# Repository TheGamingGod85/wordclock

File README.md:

# Wordclock
ESP32 based DIY wordclock project

> **60 cm fork:** see the [60 cm Full Build Guide](README-60cm.md) for the enlarged two-LED-per-letter version, or the [short plan](PLAN-60cm.md) for the decision list.

TL;DR: check out this :sparkles:[demo video](https://youtu.be/WF_X5soabm0) :sparkles:

<br/>
Another take on the classic DIY word clock. This one requires a laser cutter but promises a very clean result and is quite cheap to make (about 50 €) while being feature packed with its 11x10 RGB LED matrix, RTC module (time setting survives power loss), light sensor, WiFi connectivity and more. 

This project was designed for the tools available in our makerspace. The largest square that can be cut in an Epilog Mini laser cutter is approximately 30x30cm, so the clock is designed around that constraint.

<br/>

## Table of Contents

- [Project overview](#project-overview)
  * [Hardware](#hardware)
  * [Software](#software)
- [Bill Of Materials](#bill-of-materials)
  * [Electronics](#electronics)
  * [Frame](#frame)

## Project overview

### Hardware 

Building the clock from scratch involves mostly laser cutting and soldering. It is not technically challenging if you have basic soldering skills (and access to a laser cutter), but it does take time on both fronts. The project's hardware can be broken down in 3 major elements:

- __The faceplate__ is a glass panel from a cheap picture frame, that is spray painted on its back, then laser etched to mark the letters. The templates and instructions are located in [the faceplate subdirectory](hardware/faceplate/README.md).
- __The frame__ is a sandwich of laser-cut MDF boards. If could also be done with CEC or 3d printing. It holds everything together and most importantly the LED matrix. It has little wells for each LED to channel the light to the letters on the faceplate. The templates and assembly instructions are located in [the frame subdirectory](hardware/frame/README.md).
- __The electronics__ revolve around a WiFI enabled ESP32 development board and a matrix of 114 LEDs made from an LED strip. There is also an RTC module to keep track of time, and a light sensor (LDR). The schematics and instructions for assembly are located in [the electronics subdirectory](hardware/electronics/README.md).

You can oviously choose to customize any of the provided templates to eg create a different faceplate, or adapt the frame to your specific needs (change the LED layout, add extra sensors, etc).

#### Nodo clock

Alternatively, [nodo-shop.nl](https://nodo-shop.nl) developed and sells [a kit](https://www.nodo-shop.nl/en/52-wordclock) that is fully compatible with the software side of this project. 

The kit includes a 3D-printed faceplate (EN, FR and NL versions available) and custom circuit board, is very simple to assemble and requires no soldering.

### Software

The provided [source code](software/README.md) is using [PlatformIO](https://platformio.org/) and Arduino IDE. Here's a [demo video](https://youtu.be/WF_X5soabm0) (from v1.0, does not show all current features).

It runs a web server though a WiFi captive portal for initial configuration via a smartphone or computer, then optionally connects to your home network to use internet time (NTP), MQTT client for home automation, and other features. Check out the [User's Manual](software/UsersManual.md) for more details.

It is, of course, possible to ditch that code entirely and use [ESPHome](https://esphome.io/) or [MicroPython](https://docs.micropython.org/en/latest/esp32/tutorial/intro.html) instead. 

## Bill Of Materials

### Electronics

| Designation | Sample purchase link | Price |  
| ----------- | -------------------- | ----- |  
| ESP32 (WROOM32) microcontroller | [amazon.fr](https://www.amazon.fr/gp/product/B06XWVS2SJ/ref=ox_sc_act_title_6?smid=A3OY00ITR6XRNR&psc=1) | 5,99 € |
| DS3231 RTC module | [amazon.fr](https://www.amazon.fr/gp/product/B07DK5M5VW/) | 3,66 € |
| Level shifter 3.3 -> 5v | [amazon.fr](https://www.amazon.fr/gp/product/B07LG6RK7L) | 0,80 € |
| RGB addressable LEDs (WS2812), 60 per meter, 2 meters roll | [aliexpress.com](https://www.aliexpress.com/item/32958709980.html?spm=2114.search0104.3.35.2a616adcbmvvSU&ws_ab_test=searchweb0_0%2Csearchweb201602_4_10065_10130_10068_10547_319_317_10545_10696_10084_453_454_10083_10618_10307_10821_537_10302_536_10059_10884_10887_321_322_10103%2Csearchweb201603_53%2CppcSwitch_0&algo_expid=2a4f6a2a-c5bc-4435-a3ff-21b692aed5ff-7&algo_pvid=2a4f6a2a-c5bc-4435-a3ff-21b692aed5ff) | 4,17 € |
| 1000 uF capacitor | [amazon.fr](https://www.amazon.fr/gp/product/B01M4IUST7) | 0,40 € |
| Power supply (5V, 6A) | [aliexpress.com](https://fr.aliexpress.com/item/32835554243.html) | 6,99 € |
| Female barrel plug | [amazon.fr](https://www.amazon.fr/gp/product/B06XPBKC37) | 0,86 € |
| Light dependent resistor (LDR 5537) | [amazon.fr](https://www.amazon.fr/gp/product/B074QLFCF6/) | 0,08 € |
| Resistor 10k |
| Perfboard | [conrad.fr](https://www.conrad.fr/p/platine-dexperimentation-rademacher-wr-typ-908-1-vk-c-908-1-ep-epoxy-l-x-l-80-mm-x-50-mm-35-m-pas-254-mm-1-pcs-527309) | 3,36 € |
| Breakaway header pins | [amazon.fr](https://www.amazon.fr/gp/product/B07C3W8DGZ/ref=ppx_yo_dt_b_asin_title_o03_s00?ie=UTF8&psc=1) | 0,14 € |
| Wiring (silicon coating is recommended) |
| Solder |  
| Kapton + Electrical tape |
| Heatshrink tubing |
| Hot glue gun + glue sticks |

### Frame

| Designation | Sample purchase link | Price |  
| ----------- | -------------------- | ----- | 
| MDF boards, ~30.5 cm by 30.5+ cm, 3mm and 6mm thick | 615mm x 310mm boards, cut at Leroy Merlin | 5€ |
| Picture frame with glass panel, 30 by 30 cm | [leroymerlin.fr](https://www.leroymerlin.fr/v3/p/produits/cadre-clip-30-x-30-cm-e1500701594) | 2,99 € |
| Wood glue |
| Clamps |
| Spray paint (acrylic) |
| Edgeband |
| 1mm black felt layer | [amazon.fr](https://www.amazon.fr/dp/B07LFJNLZ9/) | 1,11 € |
| Ultra low profile VELCRO® strip or similar | [amazon.fr](https://www.amazon.fr/dp/B0728LKFGM/ref=pe_3044141_189395771_TE_dp_1) | 26 € |
| Black adhesive vinyl (just a small sheet) |
| Copper tape 51mm X 20m (optional) | [amazon.fr](https://www.amazon.fr/gp/product/B01MTQA0O6/ref=ppx_od_dt_b_asin_title_s00?ie=UTF8&psc=1) | 18,98 € |

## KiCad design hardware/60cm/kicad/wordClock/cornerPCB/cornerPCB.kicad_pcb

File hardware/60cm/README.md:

# 60 cm wordclock templates

Generated from the archived 30 cm design in `hardware/_archive_30cm/`.

Run `uv run 60cm` from this folder to regenerate every SVG. It writes into the folders below.

## Folders

| Folder | What is in it |
|---|---|
| `cut/` | The files to send to the cutter. These are the ones you need. |
| `backup/` | The original stencil outlines, kept in case Allerta does not cut well. |
| `preview/` | Layer-stack overlays and the font comparison image. Preview only — never cut these. |
| `fonts/` | The Google Fonts used for the stencil and comparisons (OFL licensed). |
| `electronics/` | `wordclock_60cm.fzz` circuit and its [wiring notes](electronics/README.md). |

## Files to cut

| File | Material | Notes |
|---|---|---|
| `cut/faceplate_clear_600.svg` | clear cast acrylic | Front sheet. Includes corner LED holes and two registration holes. |
| `cut/faceplate_EN_stencil_600.svg` | black acrylic | **Production cut file.** Allerta Stencil letters; bridges stop counter pieces falling out. |
| `cut/frame_cut1_600.svg` | 3 mm MDF | LED board support, with a bottom cavity for the controller. |
| `cut/frame_cut2_lightwells_600.svg` | 6 mm MDF | 110 wells: one per letter, scaled from the original hole. |
| `cut/frame_spacers_600.svg` | 6 mm MDF | One frame; cut as many layers as needed. |
| `cut/frame_back_600.svg` | back panel | Hatch and screw holes. |

## Backup

| File | Notes |
|---|---|
| `backup/faceplate_EN_stencil_original_600.svg` | The original 30 cm-derived letter outlines, as a cut-ready file. |

## Previews

| File | Notes |
|---|---|
| `preview/overlay_600.svg` | All six layers stacked with the production Allerta letters; legend lists them front to back. |
| `preview/overlay_original_stencil_600.svg` | Same stack with the backup original outlines. |
| `preview/overlay_stencil_font_600.svg` | Same stack, letters from Windows `STENCIL.TTF`. |
| `preview/overlay_BigShouldersStencilDisplay_600.svg` | Same stack, Google Fonts "Big Shoulders Stencil Display". |
| `preview/overlay_StardosStencil-Bold_600.svg` | Same stack, Google Fonts "Stardos Stencil Bold". |
| `preview/overlay_StardosStencil-Regular_600.svg` | Same stack, Google Fonts "Stardos Stencil Regular". |
| `preview/font_compare.png` | Side-by-side sample of all five fonts. |

All cut lines are red (`#ff0000`), fill none, 0.5 mm stroke. The sheets are 600 × 600 mm.

Registration holes at (15, 300) and (585, 300) line the two face sheets up, outside the spacer inner cut line. Corner LED holes are 12 mm across.

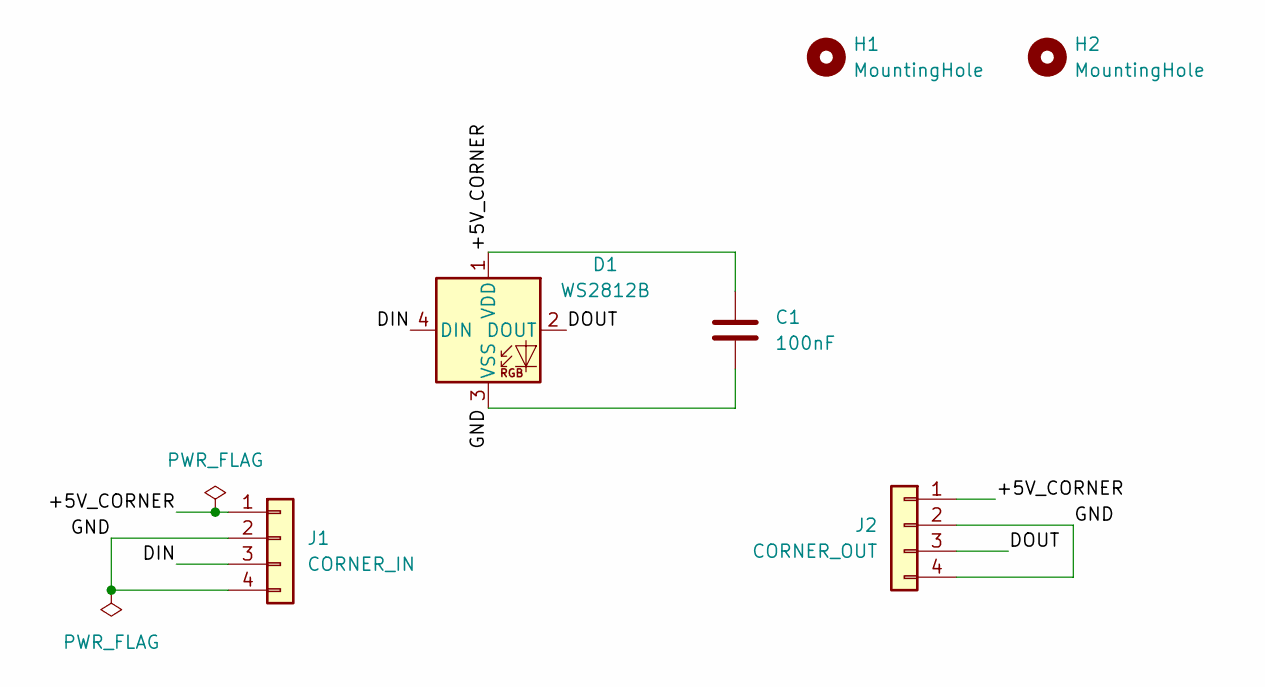
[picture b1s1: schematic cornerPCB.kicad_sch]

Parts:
C1: 100nF; C_0805_2012Metric
D1: WS2812B; LED_WS2812B_PLCC4_5.0x5.0mm_P3.2mm
H1, H2: MountingHole; MountingHole_3.2mm_M3
J1: CORNER_IN; TerminalBlock_4Ucon_1x04_P3.50mm_Horizontal
J2: CORNER_OUT; TerminalBlock_4Ucon_1x04_P3.50mm_Horizontal

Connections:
/+5V_CORNER: C1.1, D1.1 (VDD), J1.1, J2.1
/DIN: D1.4 (DIN), J1.3
/DOUT: D1.2 (DOUT), J2.3
/GND: C1.2, D1.3 (VSS), J1.2, J1.4, J2.2, J2.4

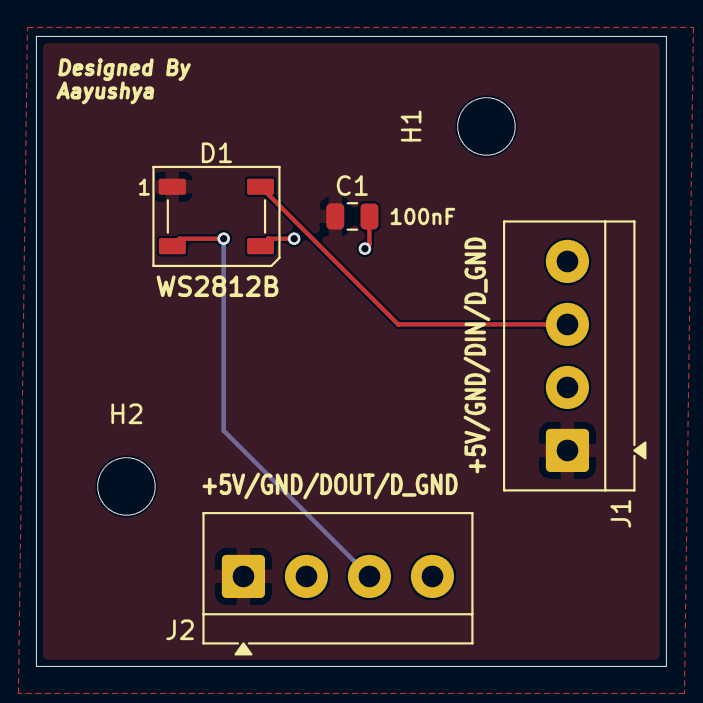
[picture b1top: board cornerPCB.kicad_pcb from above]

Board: 2 copper layers, 35.0 x 35.0 mm, 6 parts (0 on the bottom side), 4 nets.

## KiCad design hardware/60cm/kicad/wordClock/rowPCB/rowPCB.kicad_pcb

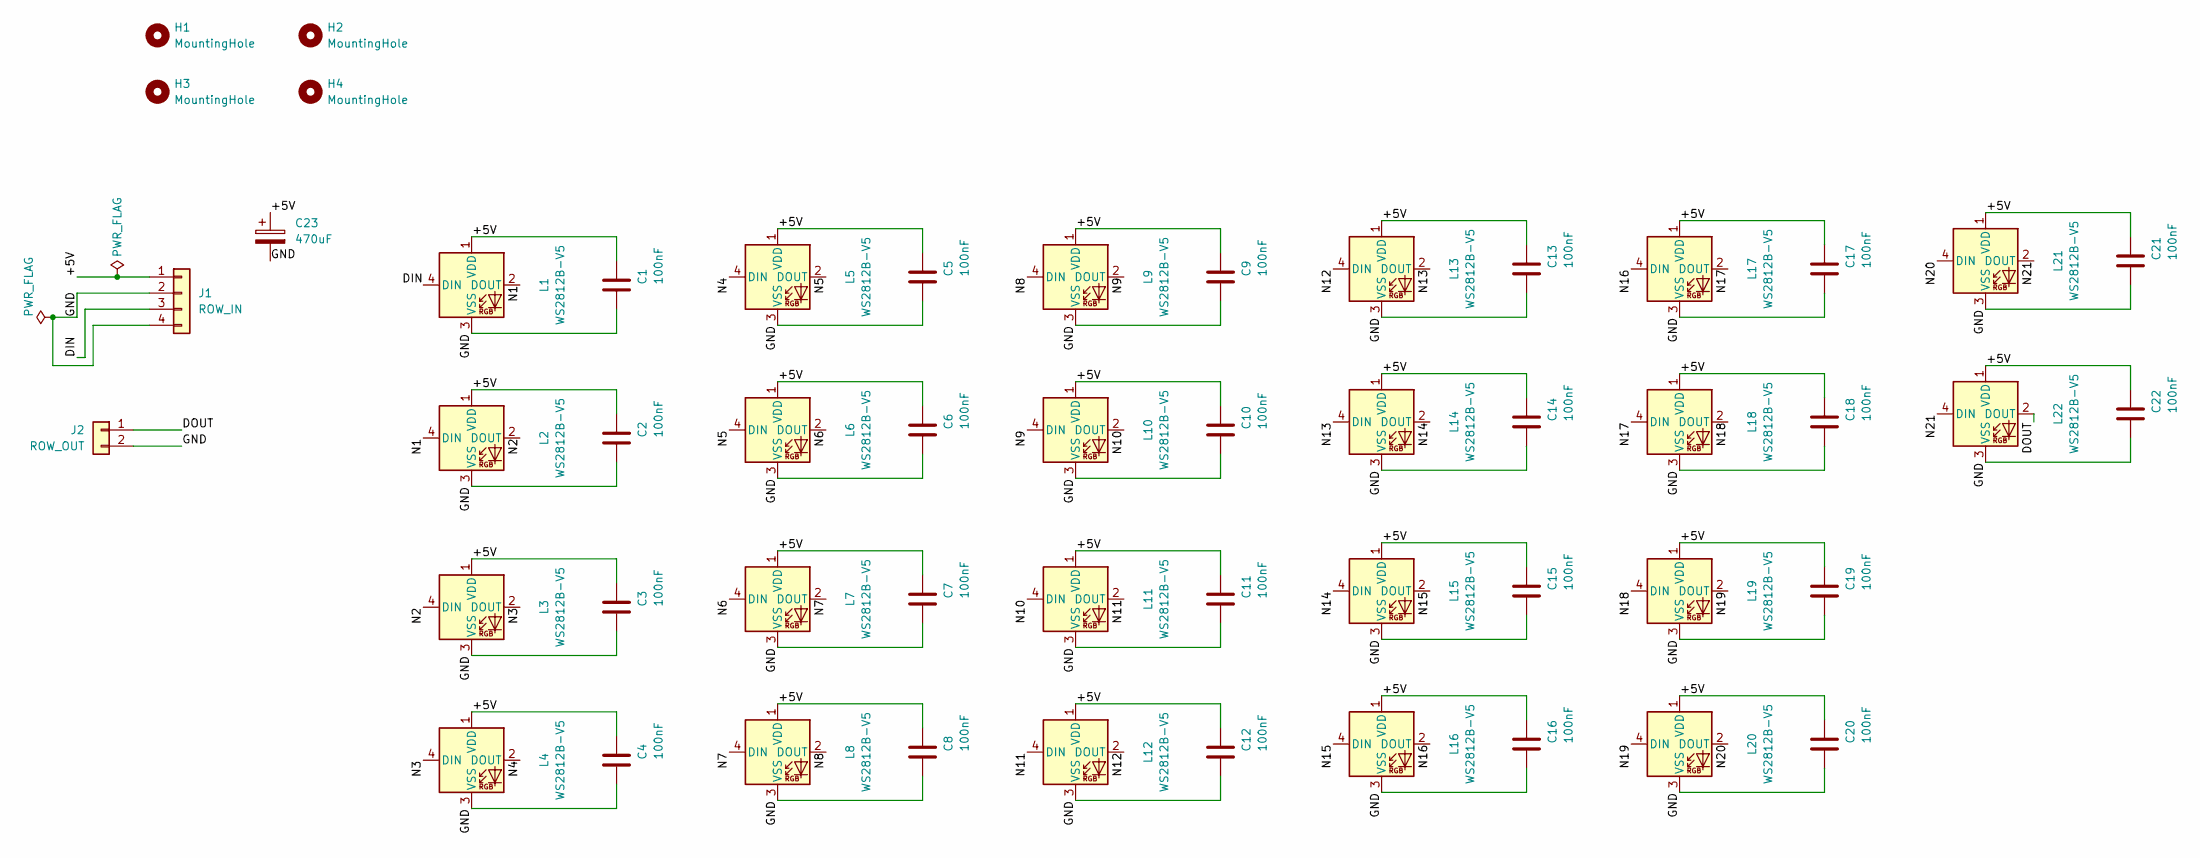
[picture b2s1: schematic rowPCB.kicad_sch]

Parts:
C1, C2, C3, C4, C5, C6, C7, C8, C9, C10, C11, C12, C13, C14, C15, C16, C17, C18, C19, C20, C21, C22: 100nF; C_0805_2012Metric
C23: 470uF; CP_Elec_8x10.5
H1, H2, H3, H4: MountingHole; MountingHole_3.2mm_M3
J1: ROW_IN; TerminalBlock_4Ucon_1x04_P3.50mm_Horizontal
J2: ROW_OUT; TerminalBlock_4Ucon_1x02_P3.50mm_Horizontal
L1, L2, L3, L4, L5, L6, L7, L8, L9, L10, L11, L12, L13, L14, L15, L16, L17, L18, L19, L20, L21, L22: WS2812B-V5; LED_WS2812B_PLCC4_5.0x5.0mm_P3.2mm

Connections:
/+5V: C1.1, C2.1, C3.1, C4.1, C5.1, C6.1, C7.1, C8.1, C9.1, C10.1, C11.1, C12.1, C13.1, C14.1, C15.1, C16.1, C17.1, C18.1, C19.1, C20.1, C21.1, C22.1, C23.1, J1.1, L1.1 (VDD), L2.1 (VDD), L3.1 (VDD), L4.1 (VDD), L5.1 (VDD), L6.1 (VDD), L7.1 (VDD), L8.1 (VDD), L9.1 (VDD), L10.1 (VDD), L11.1 (VDD), L12.1 (VDD), L13.1 (VDD), L14.1 (VDD), L15.1 (VDD), L16.1 (VDD), L17.1 (VDD), L18.1 (VDD), L19.1 (VDD), L20.1 (VDD), L21.1 (VDD), L22.1 (VDD)
/DIN: J1.3, L1.4 (DIN)
/DOUT: J2.1, L22.2 (DOUT)
/GND: C1.2, C2.2, C3.2, C4.2, C5.2, C6.2, C7.2, C8.2, C9.2, C10.2, C11.2, C12.2, C13.2, C14.2, C15.2, C16.2, C17.2, C18.2, C19.2, C20.2, C21.2, C22.2, C23.2, J1.2, J1.4, J2.2, L1.3 (VSS), L2.3 (VSS), L3.3 (VSS), L4.3 (VSS), L5.3 (VSS), L6.3 (VSS), L7.3 (VSS), L8.3 (VSS), L9.3 (VSS), L10.3 (VSS), L11.3 (VSS), L12.3 (VSS), L13.3 (VSS), L14.3 (VSS), L15.3 (VSS), L16.3 (VSS), L17.3 (VSS), L18.3 (VSS), L19.3 (VSS), L20.3 (VSS), L21.3 (VSS), L22.3 (VSS)
/N1: L1.2 (DOUT), L2.4 (DIN)
/N2: L2.2 (DOUT), L3.4 (DIN)
/N3: L3.2 (DOUT), L4.4 (DIN)
/N4: L4.2 (DOUT), L5.4 (DIN)
/N5: L5.2 (DOUT), L6.4 (DIN)
/N6: L6.2 (DOUT), L7.4 (DIN)
/N7: L7.2 (DOUT), L8.4 (DIN)
/N8: L8.2 (DOUT), L9.4 (DIN)
/N9: L9.2 (DOUT), L10.4 (DIN)
/N10: L10.2 (DOUT), L11.4 (DIN)
/N11: L11.2 (DOUT), L12.4 (DIN)
/N12: L12.2 (DOUT), L13.4 (DIN)
/N13: L13.2 (DOUT), L14.4 (DIN)
/N14: L14.2 (DOUT), L15.4 (DIN)
/N15: L15.2 (DOUT), L16.4 (DIN)
/N16: L16.2 (DOUT), L17.4 (DIN)
/N17: L17.2 (DOUT), L18.4 (DIN)
/N18: L18.2 (DOUT), L19.4 (DIN)
/N19: L19.2 (DOUT), L20.4 (DIN)
/N20: L20.2 (DOUT), L21.4 (DIN)
/N21: L21.2 (DOUT), L22.4 (DIN)

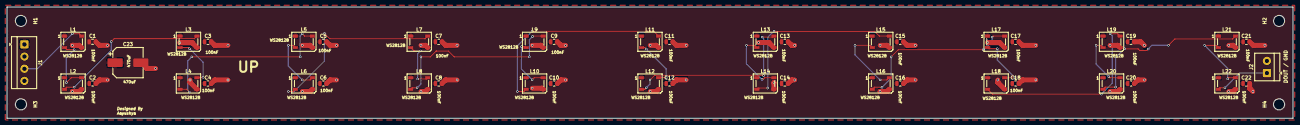
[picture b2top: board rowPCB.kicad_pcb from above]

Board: 2 copper layers, 370.0 x 32.0 mm, 51 parts (0 on the bottom side), 25 nets.

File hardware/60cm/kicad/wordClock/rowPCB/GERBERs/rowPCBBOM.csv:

"Reference","Qty","Value","DNP","Exclude from BOM","Exclude from Board","Exclude from Simulation","Exclude from Position Files","Footprint","Datasheet"
"L1,L2,L3,L4,L5,L6,L7,L8,L9,L10,L11,L12,L13,L14,L15,L16,L17,L18,L19,L20,L21,L22","22","WS2812B-V5","","","","","${EXCLUDE_FROM_POS_FILES}","LED_SMD:LED_WS2812B_PLCC4_5.0x5.0mm_P3.2mm","https://cdn-shop.adafruit.com/datasheets/WS2812B.pdf"
"C1,C2,C3,C4,C5,C6,C7,C8,C9,C10,C11,C12,C13,C14,C15,C16,C17,C18,C19,C20,C21,C22","22","100nF","","","","","${EXCLUDE_FROM_POS_FILES}","Capacitor_SMD:C_0805_2012Metric",""
"J2","1","ROW_OUT","","","","","${EXCLUDE_FROM_POS_FILES}","TerminalBlock_4Ucon:TerminalBlock_4Ucon_1x02_P3.50mm_Horizontal",""
"J1","1","ROW_IN","","","","","${EXCLUDE_FROM_POS_FILES}","TerminalBlock_4Ucon:TerminalBlock_4Ucon_1x04_P3.50mm_Horizontal",""
"C23","1","470uF","","","","","${EXCLUDE_FROM_POS_FILES}","Capacitor_SMD:CP_Elec_8x10.5",""

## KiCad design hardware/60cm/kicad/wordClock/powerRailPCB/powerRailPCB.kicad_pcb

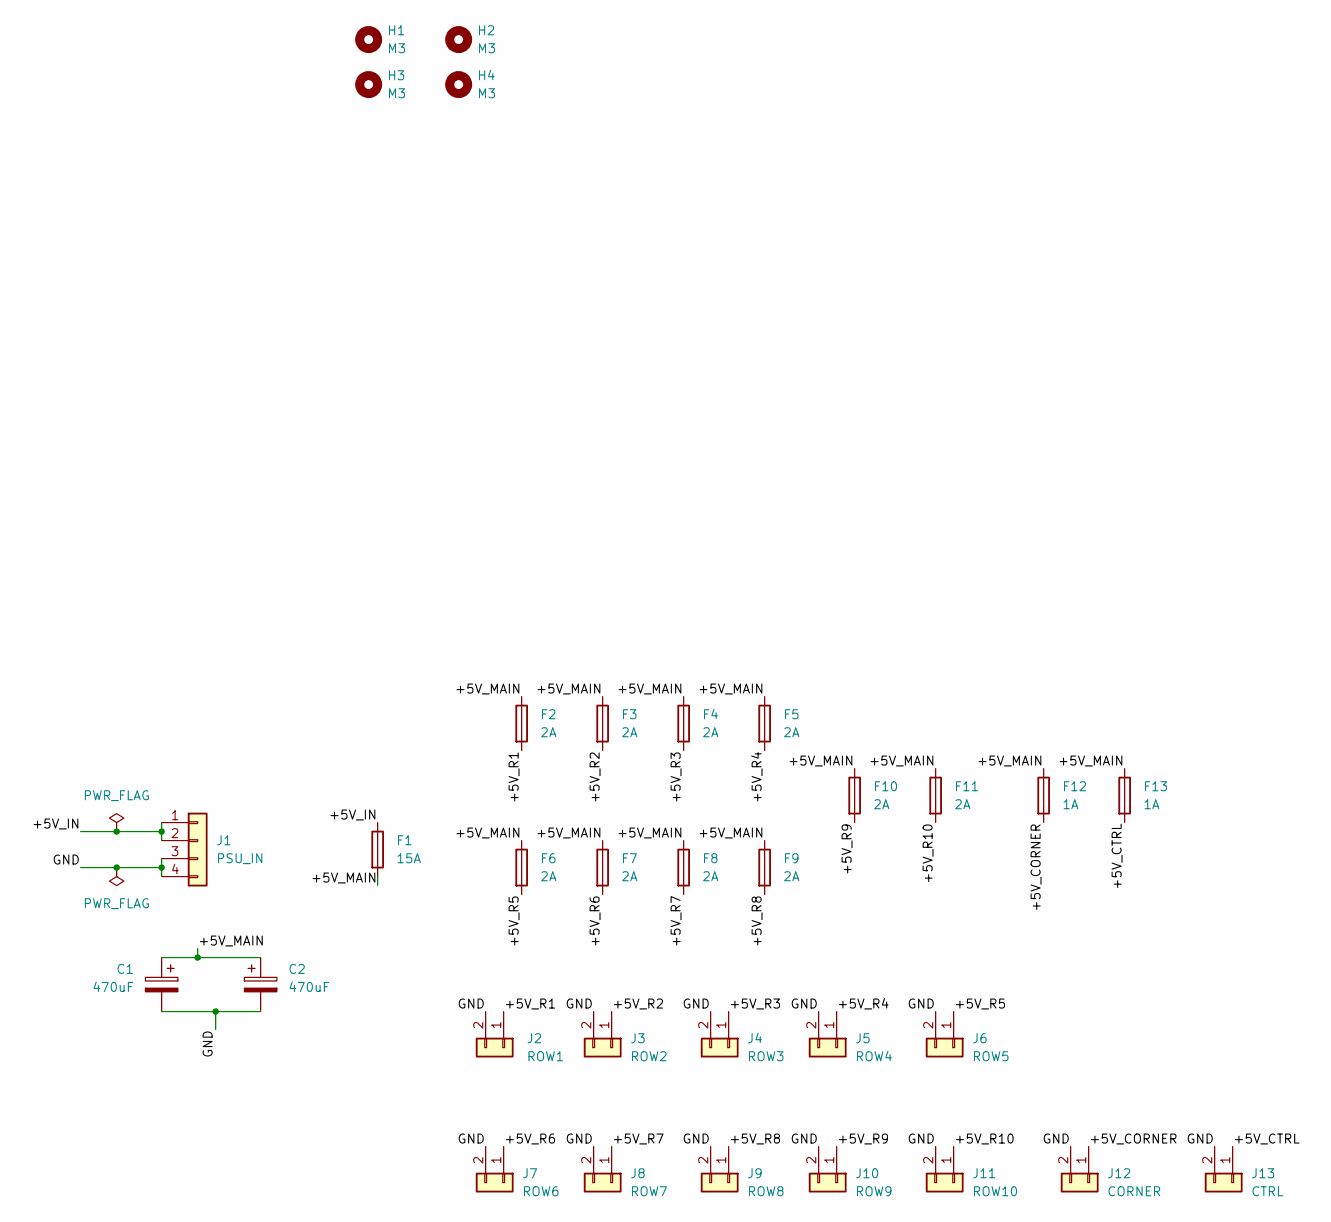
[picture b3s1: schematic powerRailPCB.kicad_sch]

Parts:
C1, C2: 470uF; CP_Elec_8x10.5
F1: 15A; Fuseholder_Blade_Mini_Keystone_3568
F2, F3, F4, F5, F6, F7, F8, F9, F10, F11: 2A; Fuseholder_Blade_Mini_Keystone_3568
F12, F13: 1A; Fuseholder_Blade_Mini_Keystone_3568
H1, H2, H3, H4: M3; MountingHole_3.2mm_M3
J1: PSU_IN; TerminalBlock_4Ucon_1x04_P3.50mm_Horizontal
J2: ROW1; TerminalBlock_4Ucon_1x02_P3.50mm_Horizontal
J3: ROW2; TerminalBlock_4Ucon_1x02_P3.50mm_Horizontal
J4: ROW3; TerminalBlock_4Ucon_1x02_P3.50mm_Horizontal
J5: ROW4; TerminalBlock_4Ucon_1x02_P3.50mm_Horizontal
J6: ROW5; TerminalBlock_4Ucon_1x02_P3.50mm_Horizontal
J7: ROW6; TerminalBlock_4Ucon_1x02_P3.50mm_Horizontal
J8: ROW7; TerminalBlock_4Ucon_1x02_P3.50mm_Horizontal
J9: ROW8; TerminalBlock_4Ucon_1x02_P3.50mm_Horizontal
J10: ROW9; TerminalBlock_4Ucon_1x02_P3.50mm_Horizontal
J11: ROW10; TerminalBlock_4Ucon_1x02_P3.50mm_Horizontal
J12: CORNER; TerminalBlock_4Ucon_1x02_P3.50mm_Horizontal
J13: CTRL; TerminalBlock_4Ucon_1x02_P3.50mm_Horizontal

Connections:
/+5V_CORNER: F12.2, J12.1
/+5V_CTRL: F13.2, J13.1
/+5V_IN: F1.1, J1.1, J1.2
/+5V_MAIN: C1.1, C2.1, F1.2, F2.1, F3.1, F4.1, F5.1, F6.1, F7.1, F8.1, F9.1, F10.1, F11.1, F12.1, F13.1
/+5V_R1: F2.2, J2.1
/+5V_R2: F3.2, J3.1
/+5V_R3: F4.2, J4.1
/+5V_R4: F5.2, J5.1
/+5V_R5: F6.2, J6.1
/+5V_R6: F7.2, J7.1
/+5V_R7: F8.2, J8.1
/+5V_R8: F9.2, J9.1
/+5V_R9: F10.2, J10.1
/+5V_R10: F11.2, J11.1
/GND: C1.2, C2.2, J1.3, J1.4, J2.2, J3.2, J4.2, J5.2, J6.2, J7.2, J8.2, J9.2, J10.2, J11.2, J12.2, J13.2

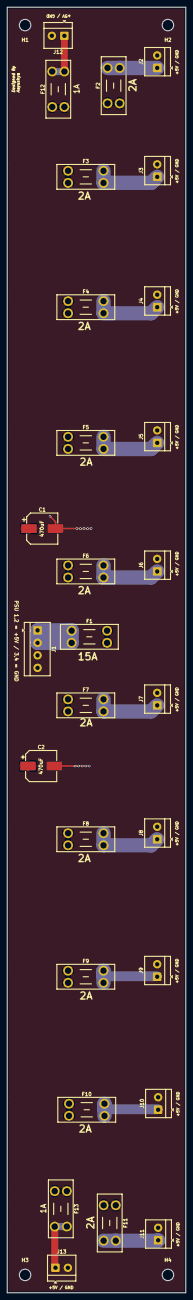
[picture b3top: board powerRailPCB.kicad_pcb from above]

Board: 2 copper layers, 50.0 x 360.0 mm, 32 parts (0 on the bottom side), 15 nets.

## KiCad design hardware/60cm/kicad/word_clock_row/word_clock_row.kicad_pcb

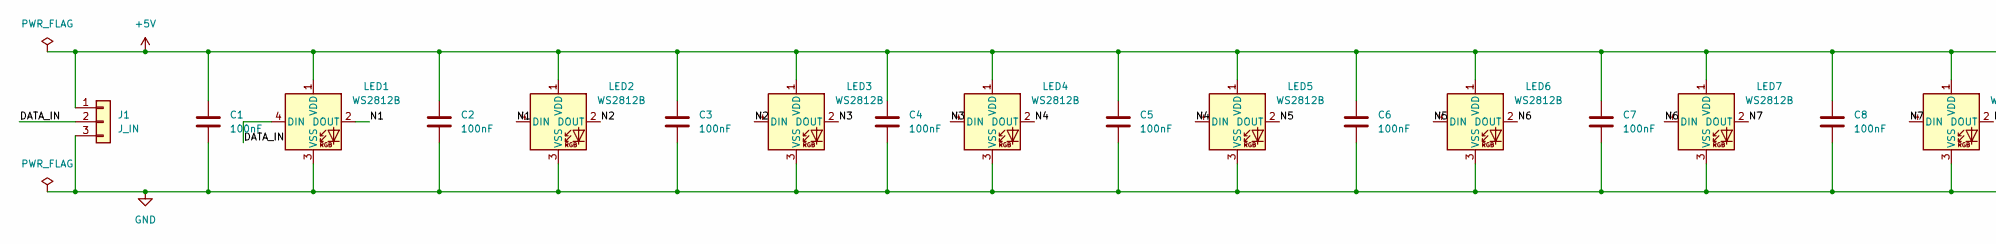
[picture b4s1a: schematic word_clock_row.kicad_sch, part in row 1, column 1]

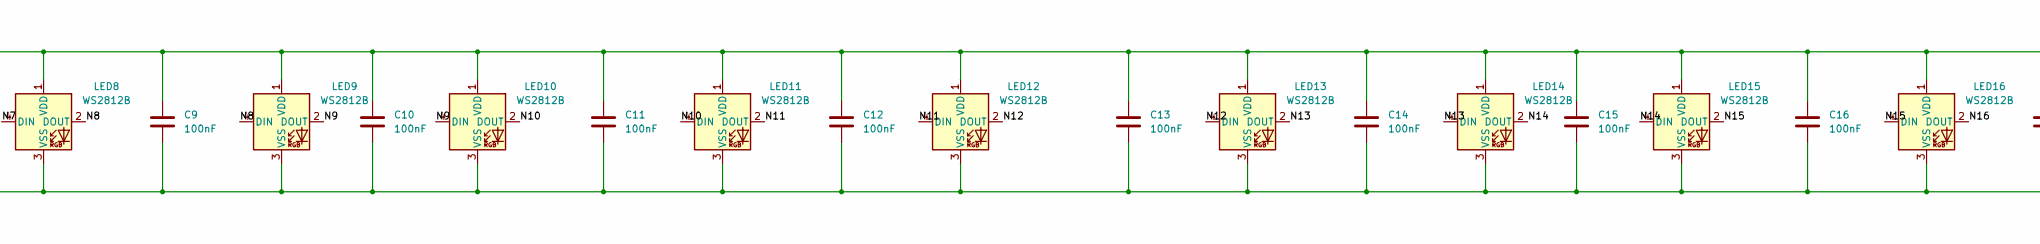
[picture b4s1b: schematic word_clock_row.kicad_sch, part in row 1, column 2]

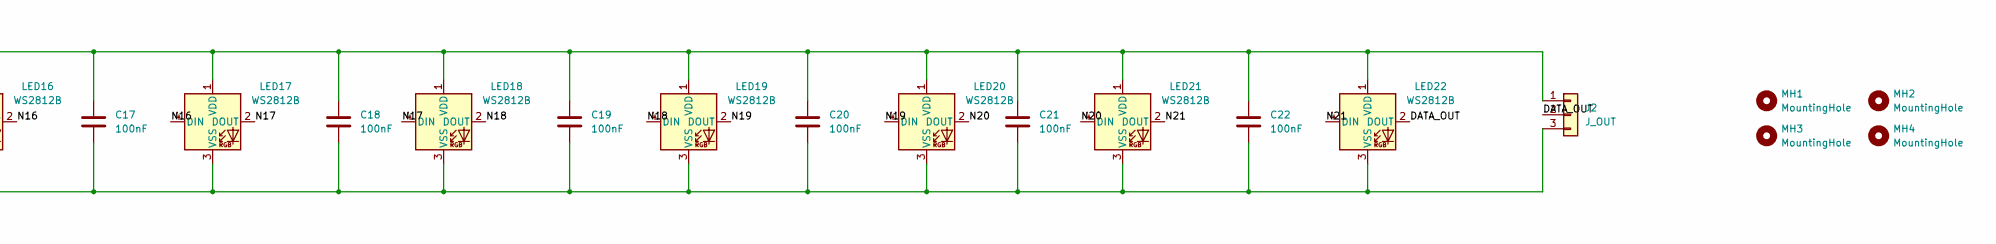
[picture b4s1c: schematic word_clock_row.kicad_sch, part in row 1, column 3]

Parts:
C1, C2, C3, C4, C5, C6, C7, C8, C9, C10, C11, C12, C13, C14, C15, C16, C17, C18, C19, C20, C21, C22: 100nF; C_0805_2012Metric
J1: J_IN; JST_XH_B3B-XH-A_1x03_P2.50mm_Vertical
J2: J_OUT; JST_XH_B3B-XH-A_1x03_P2.50mm_Vertical
LED1, LED2, LED3, LED4, LED5, LED6, LED7, LED8, LED9, LED10, LED11, LED12, LED13, LED14, LED15, LED16, LED17, LED18, LED19, LED20, LED21, LED22: WS2812B; LED_WS2812B_PLCC4_5.0x5.0mm_P3.2mm
MH1, MH2, MH3, MH4: MountingHole; MountingHole_3.2mm_M3

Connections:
+5V: C1.2, C2.2, C3.2, C4.2, C5.2, C6.2, C7.2, C8.2, C9.2, C10.2, C11.2, C12.2, C13.2, C14.2, C15.2, C16.2, C17.2, C18.2, C19.2, C20.2, C21.2, C22.2, J1.1, J2.1, LED1.1 (VDD), LED2.1 (VDD), LED3.1 (VDD), LED4.1 (VDD), LED5.1 (VDD), LED6.1 (VDD), LED7.1 (VDD), LED8.1 (VDD), LED9.1 (VDD), LED10.1 (VDD), LED11.1 (VDD), LED12.1 (VDD), LED13.1 (VDD), LED14.1 (VDD), LED15.1 (VDD), LED16.1 (VDD), LED17.1 (VDD), LED18.1 (VDD), LED19.1 (VDD), LED20.1 (VDD), LED21.1 (VDD), LED22.1 (VDD)
/DATA_IN: J1.2, LED1.4 (DIN)
/DATA_OUT: J2.2, LED22.2 (DOUT)
/N1: LED1.2 (DOUT), LED2.4 (DIN)
/N2: LED2.2 (DOUT), LED3.4 (DIN)
/N3: LED3.2 (DOUT), LED4.4 (DIN)
/N4: LED4.2 (DOUT), LED5.4 (DIN)
/N5: LED5.2 (DOUT), LED6.4 (DIN)
/N6: LED6.2 (DOUT), LED7.4 (DIN)
/N7: LED7.2 (DOUT), LED8.4 (DIN)
/N8: LED8.2 (DOUT), LED9.4 (DIN)
/N9: LED9.2 (DOUT), LED10.4 (DIN)
/N10: LED10.2 (DOUT), LED11.4 (DIN)
/N11: LED11.2 (DOUT), LED12.4 (DIN)
/N12: LED12.2 (DOUT), LED13.4 (DIN)
/N13: LED13.2 (DOUT), LED14.4 (DIN)
/N14: LED14.2 (DOUT), LED15.4 (DIN)
/N15: LED15.2 (DOUT), LED16.4 (DIN)
/N16: LED16.2 (DOUT), LED17.4 (DIN)
/N17: LED17.2 (DOUT), LED18.4 (DIN)
/N18: LED18.2 (DOUT), LED19.4 (DIN)
/N19: LED19.2 (DOUT), LED20.4 (DIN)
/N20: LED20.2 (DOUT), LED21.4 (DIN)
/N21: LED21.2 (DOUT), LED22.4 (DIN)
GND: C1.1, C2.1, C3.1, C4.1, C5.1, C6.1, C7.1, C8.1, C9.1, C10.1, C11.1, C12.1, C13.1, C14.1, C15.1, C16.1, C17.1, C18.1, C19.1, C20.1, C21.1, C22.1, J1.3, J2.3, LED1.3 (VSS), LED2.3 (VSS), LED3.3 (VSS), LED4.3 (VSS), LED5.3 (VSS), LED6.3 (VSS), LED7.3 (VSS), LED8.3 (VSS), LED9.3 (VSS), LED10.3 (VSS), LED11.3 (VSS), LED12.3 (VSS), LED13.3 (VSS), LED14.3 (VSS), LED15.3 (VSS), LED16.3 (VSS), LED17.3 (VSS), LED18.3 (VSS), LED19.3 (VSS), LED20.3 (VSS), LED21.3 (VSS), LED22.3 (VSS)

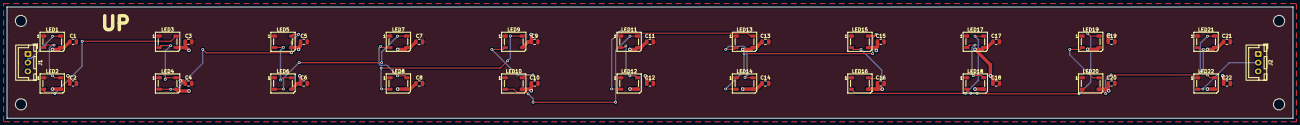
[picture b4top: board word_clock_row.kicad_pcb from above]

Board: 2 copper layers, 370.0 x 32.0 mm, 50 parts (0 on the bottom side), 25 nets.
